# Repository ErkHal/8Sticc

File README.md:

# 8Sticc
Smol 8-switch macropad. Uses a Pro Micro board and works with QMK Firmware.

# Layouts

### 8-key

### 6 + 1x2u

# BOM  
* Arduino Pro Micro (or equivalent like Elite-C, Proton-C etc.)
* 7-8 SMD Diodes
* 7-8 Cherry MX Switches (PCB-mount if you don't get a plate)

# Order pcb
You can find the gerber zip file in the gerber folder, just drop that into the manufacturer's website file upload.

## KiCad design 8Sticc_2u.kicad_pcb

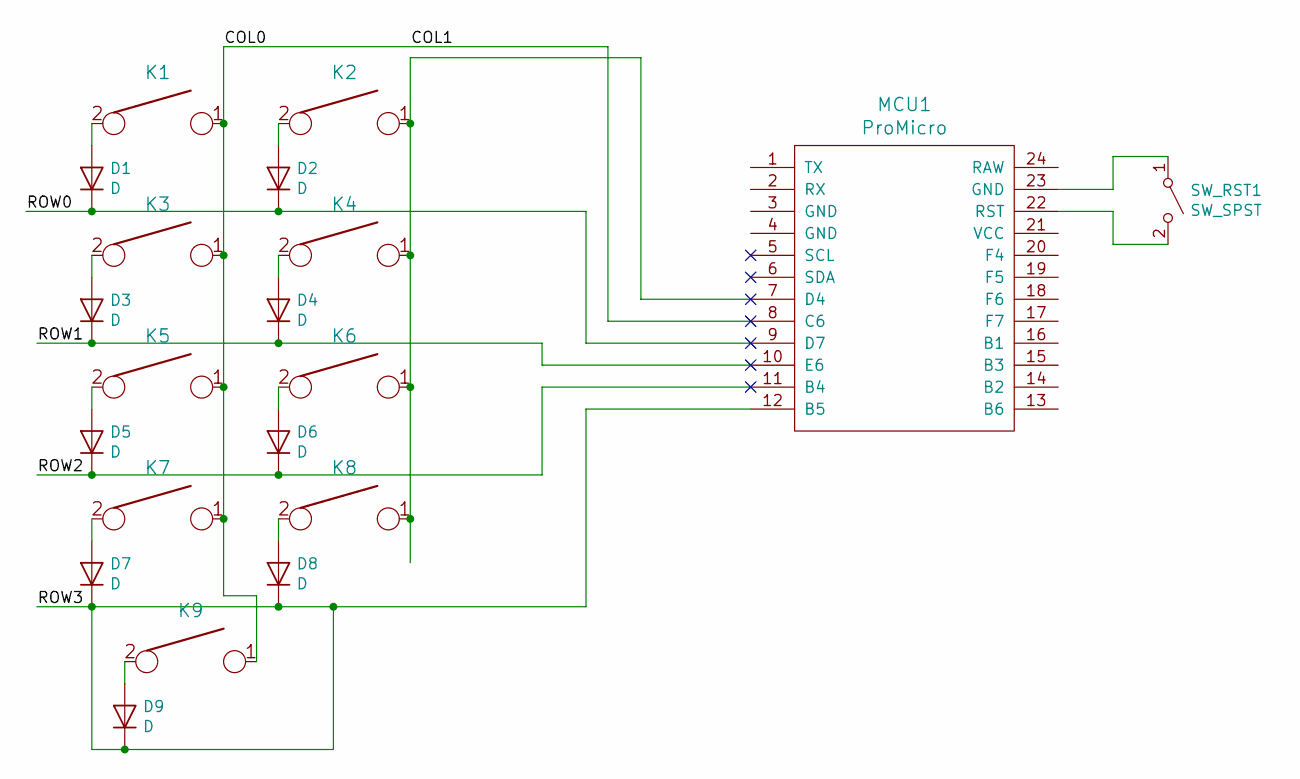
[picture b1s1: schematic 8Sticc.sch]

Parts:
D1, D2, D3, D4, D5, D6, D7, D8, D9: D; D_SOD123_hand
K1, K2, K3, K4, K5, K6, K7, K8: KEYSW; SW_Cherry_MX1A_1.00u_PCB
K9: KEYSW; SW_Cherry_MX1A_2.00u_PCB
MCU1: ProMicro
SW_RST1: SW_SPST; SW_SPST_TL3342

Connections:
/COL0: K1.1, K3.1, K5.1, K7.1, K9.1, MCU1.8 (C6)
/ROW0: D1.1 (K), D2.1 (K), MCU1.9 (D7)
/ROW1: D3.1 (K), D4.1 (K), MCU1.10 (E6)
/ROW2: D5.1 (K), D6.1 (K), MCU1.11 (B4)
/ROW3: D7.1 (K), D8.1 (K), D9.1 (K), MCU1.12 (B5)
unnamed: D1.2 (A), K1.2
unnamed: D2.2 (A), K2.2
unnamed: D3.2 (A), K3.2
unnamed: D4.2 (A), K4.2
unnamed: D5.2 (A), K5.2
unnamed: D6.2 (A), K6.2
unnamed: D7.2 (A), K7.2
unnamed: D8.2 (A), K8.2
unnamed: D9.2 (A), K9.2
unnamed: K2.1, K4.1, K6.1, K8.1, MCU1.7 (D4)
unnamed: MCU1.22 (RST), SW_RST1.2 (B)
unnamed: MCU1.23 (GND), SW_RST1.1 (A)

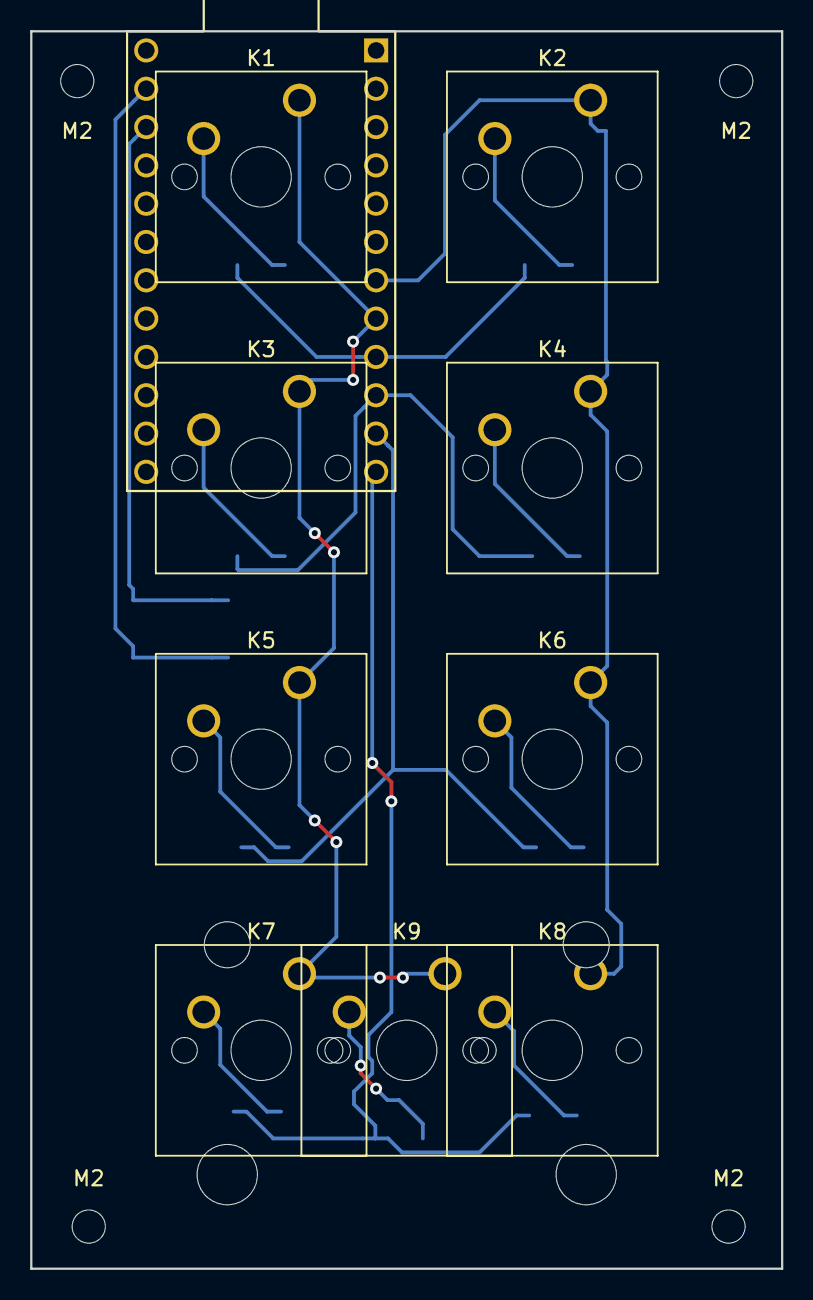
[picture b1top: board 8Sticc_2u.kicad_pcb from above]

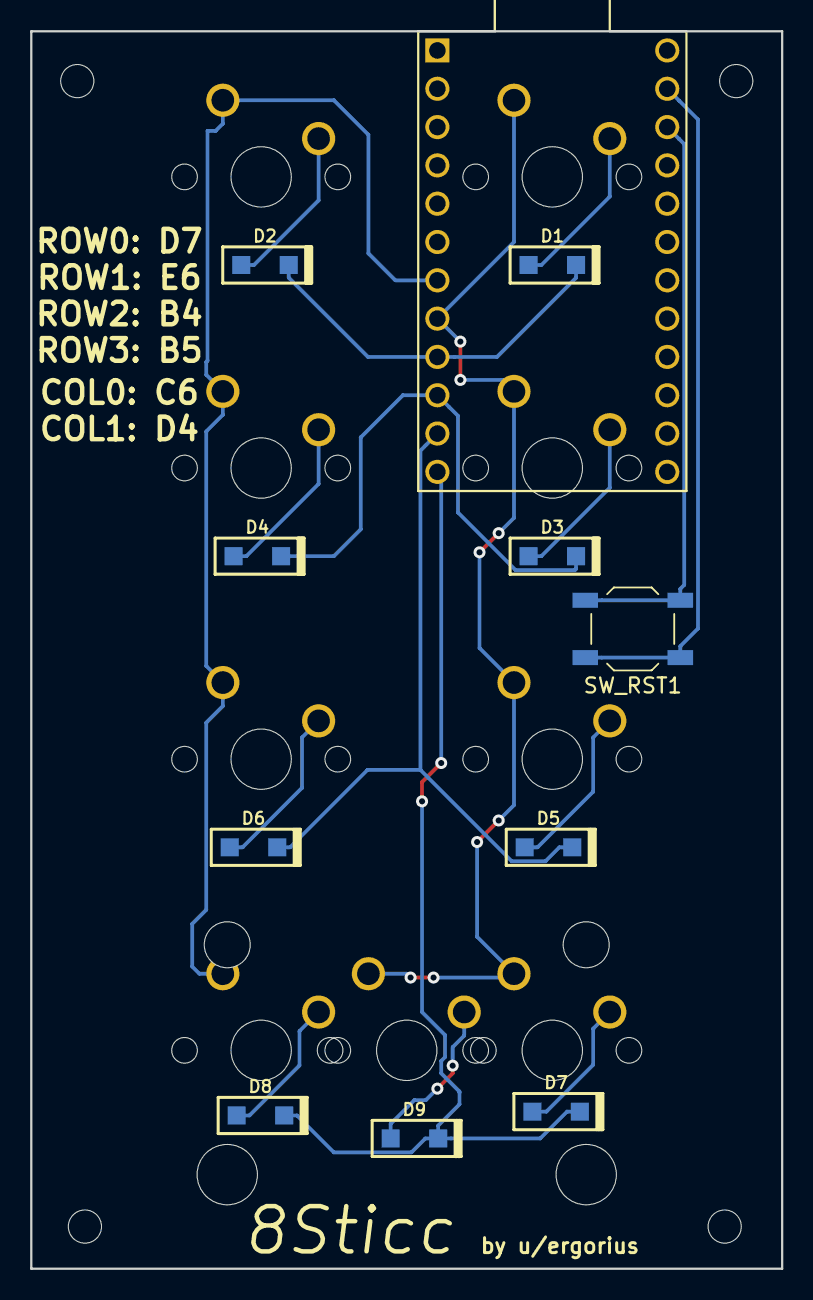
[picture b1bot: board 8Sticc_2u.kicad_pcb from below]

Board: 2 copper layers, 49.8 x 82.0 mm, 24 parts (11 on the bottom side), 17 nets.

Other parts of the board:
M2, M2#2, M2#3, M2#4: MountingHole_2.2mm_M2
